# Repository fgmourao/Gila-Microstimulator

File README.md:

# 🦎 Gila Monster 
### Constant-Current Stimulator v1.0 

> **Under development**

An electrical microstimulator for constant-current biphasic (or monophasic) stimulation. Pulse timing is generated by the firmware running on an Arduino Uno (Pulse_generator_bifasic.ino).

The hardware is based on and adapted from the [Open-Stim](https://github.com/Open-Stim/openstim) project (UFSJ / LINNCE). In the original architecture, four Arduino outputs (Timer4) time the pulses with 10 µs resolution, and the analog circuit combines these signals into a controlled current. In the present design, only two outputs are used: the firmware directly generates the two stimulation phases, Phase A (D7) and Phase B (D8), with their edges positioned in software. Built on the [Gila-Pulse-Generator](https://github.com/fgmourao/Gila-Pulse-Generator), this version adds a second output port (D8). Every pulse of the selected engine becomes a pair: port A rises, Pulse, port A falls, Delay, port B rises, Pulse, port B falls. The two pulses never overlap, and the delay between them is programmable from 10 µs upwards. All three stimulation modes, Continuous, Burst and NPS, and both Manual and Trigger operation are preserved.<br/>

## Main Modifications

- **User interface:** The Nextion touchscreen interface (Arduino Leonardo) was replaced with a 16×2 I2C LCD and rotary encoder (Arduino Uno), reducing power consumption and simplifying assembly.

- **Battery monitor:** The LM741/zener/LED battery-monitoring circuit was removed to reduce battery consumption.

- **Amplifiers:** TL072 op-amps were replaced with OPA2197 devices, providing rail-to-rail operation, low offset, and operation up to 36 V. This makes better use of the available supply voltage and increases the output compliance range.

- **Simplified signal chain:** The two inverting summing amplifiers (four Timer4 signals) were replaced by a single differential amplifier (A − B) followed by a buffer.

- **Current adjustment:** The resistor board was replaced by a 10-turn potentiometer with a dial and range selector (1 mA, 100 µA, and 10 µA), allowing direct current adjustment and readout.

- **Power supply:** ±18 V from four 9 V batteries (one 1N4007 per rail). The voltage reference and the Arduino each have their own 9 V battery.

- **Isolation:** A digital isolator (ISO7720F) separates the Arduino from the stimulation circuit. Its output side is powered by a REF5050 reference, which fixes the pulse amplitude at 5V.

- **Output protection:** A DC-blocking capacitor (CBLK, 66 µF ceramic) and "bleeder" resistor (RBLEED, 10 MΩ) at the output, pull-down resistors on the inputs, and a passive current limiter (two 1N5304 current-regulating diodes, ~1.8 mA).

- **Output enable:** PhotoMOS relays controlled by D9 connect the electrodes only during stimulation and short them at rest.

- **Compliance alarm:** Two LEDs (one per phase) light when the load exceeds the compliance limit and the current falls below the setpoint.

## Specifications

Values below come from circuit simulation.

- **Output current:** Up to 1 mA, with selectable ranges of 1 mA, 100 µA, and 10 µA. Use the lowest range that covers the desired current (1 mA: 100 µA–1 mA; 100 µA: 10–100 µA; 10 µA: below 10 µA).

- **Maximum load at 1 mA:** Approximately 16 kΩ with a ±18 V battery supply. A working load of up to 12 kΩ is recommended.

- **Compliance voltage:** Approximately 16 V with a ±18 V battery supply, including the ~1 V drop of the current limiter.

- **Battery-dependent compliance:** Maximum load follows approximately Load_max = Compliance / Current. At 1 mA, every 1 V decrease in compliance reduces the maximum load by approximately 1 kΩ. With each rail decreasing from approximately 19 V to 14 V over battery life, the corresponding maximum load is approximately 17 kΩ to 12 kΩ.

- **Frequency:** 0.10–500 Hz (firmware-limited).

- **Minimum phase duration:** 100 µs in Continuous and Burst modes; 50 µs in NPS mode (firmware-limited).

- **Maximum phase duration:** Firmware-limited, capped at 999.99 ms in all modes.
    - Biphasic: (Period − 100 µs − Delay) / 2
    - Monophasic: Period − 100 µs
    - Hardware limit: CBLK charges as I × t / C during each phase. At 1 mA into 10 kΩ, the maximum phase is approximately 460 ms.

- **Hardware limitation, charge accumulation (monophasic only):** In monophasic mode, all charge flows in the same direction and accumulates over the pulse train; RBLEED keeps it bounded. The steady-state voltage across CBLK is approximately I × duty cycle × RBLEED, reached with a time constant of RBLEED × CBLK (~11 min). At 1 mA, 100 µs phases and 4 Hz, this settles around 4 V, which must be subtracted from the available compliance. If I × duty cycle × RBLEED exceeds the compliance margin, the output saturates before steady state is reached. In balanced biphasic mode this does not occur. For a 4 µs mismatch at 1 mA and 4 Hz, the residual is about 0.16 V.

- **Long monophasic protocols:** If the protocol requires net charge, an optional jumper can short CBLK, making the output DC-coupled. This removes the DC protection, and the current limiter and output-enable stage remain the only safeguards.

## Author

Flavio Mourao (mourao.fg@gmail.com)  
CNPq/MCTI/FNDCT Call No. 21/2024 — Grant No. 446467/2024-3  
Federal University of Minas Gerais, Brazil

Development started: November 2025  
Last update: October 2026

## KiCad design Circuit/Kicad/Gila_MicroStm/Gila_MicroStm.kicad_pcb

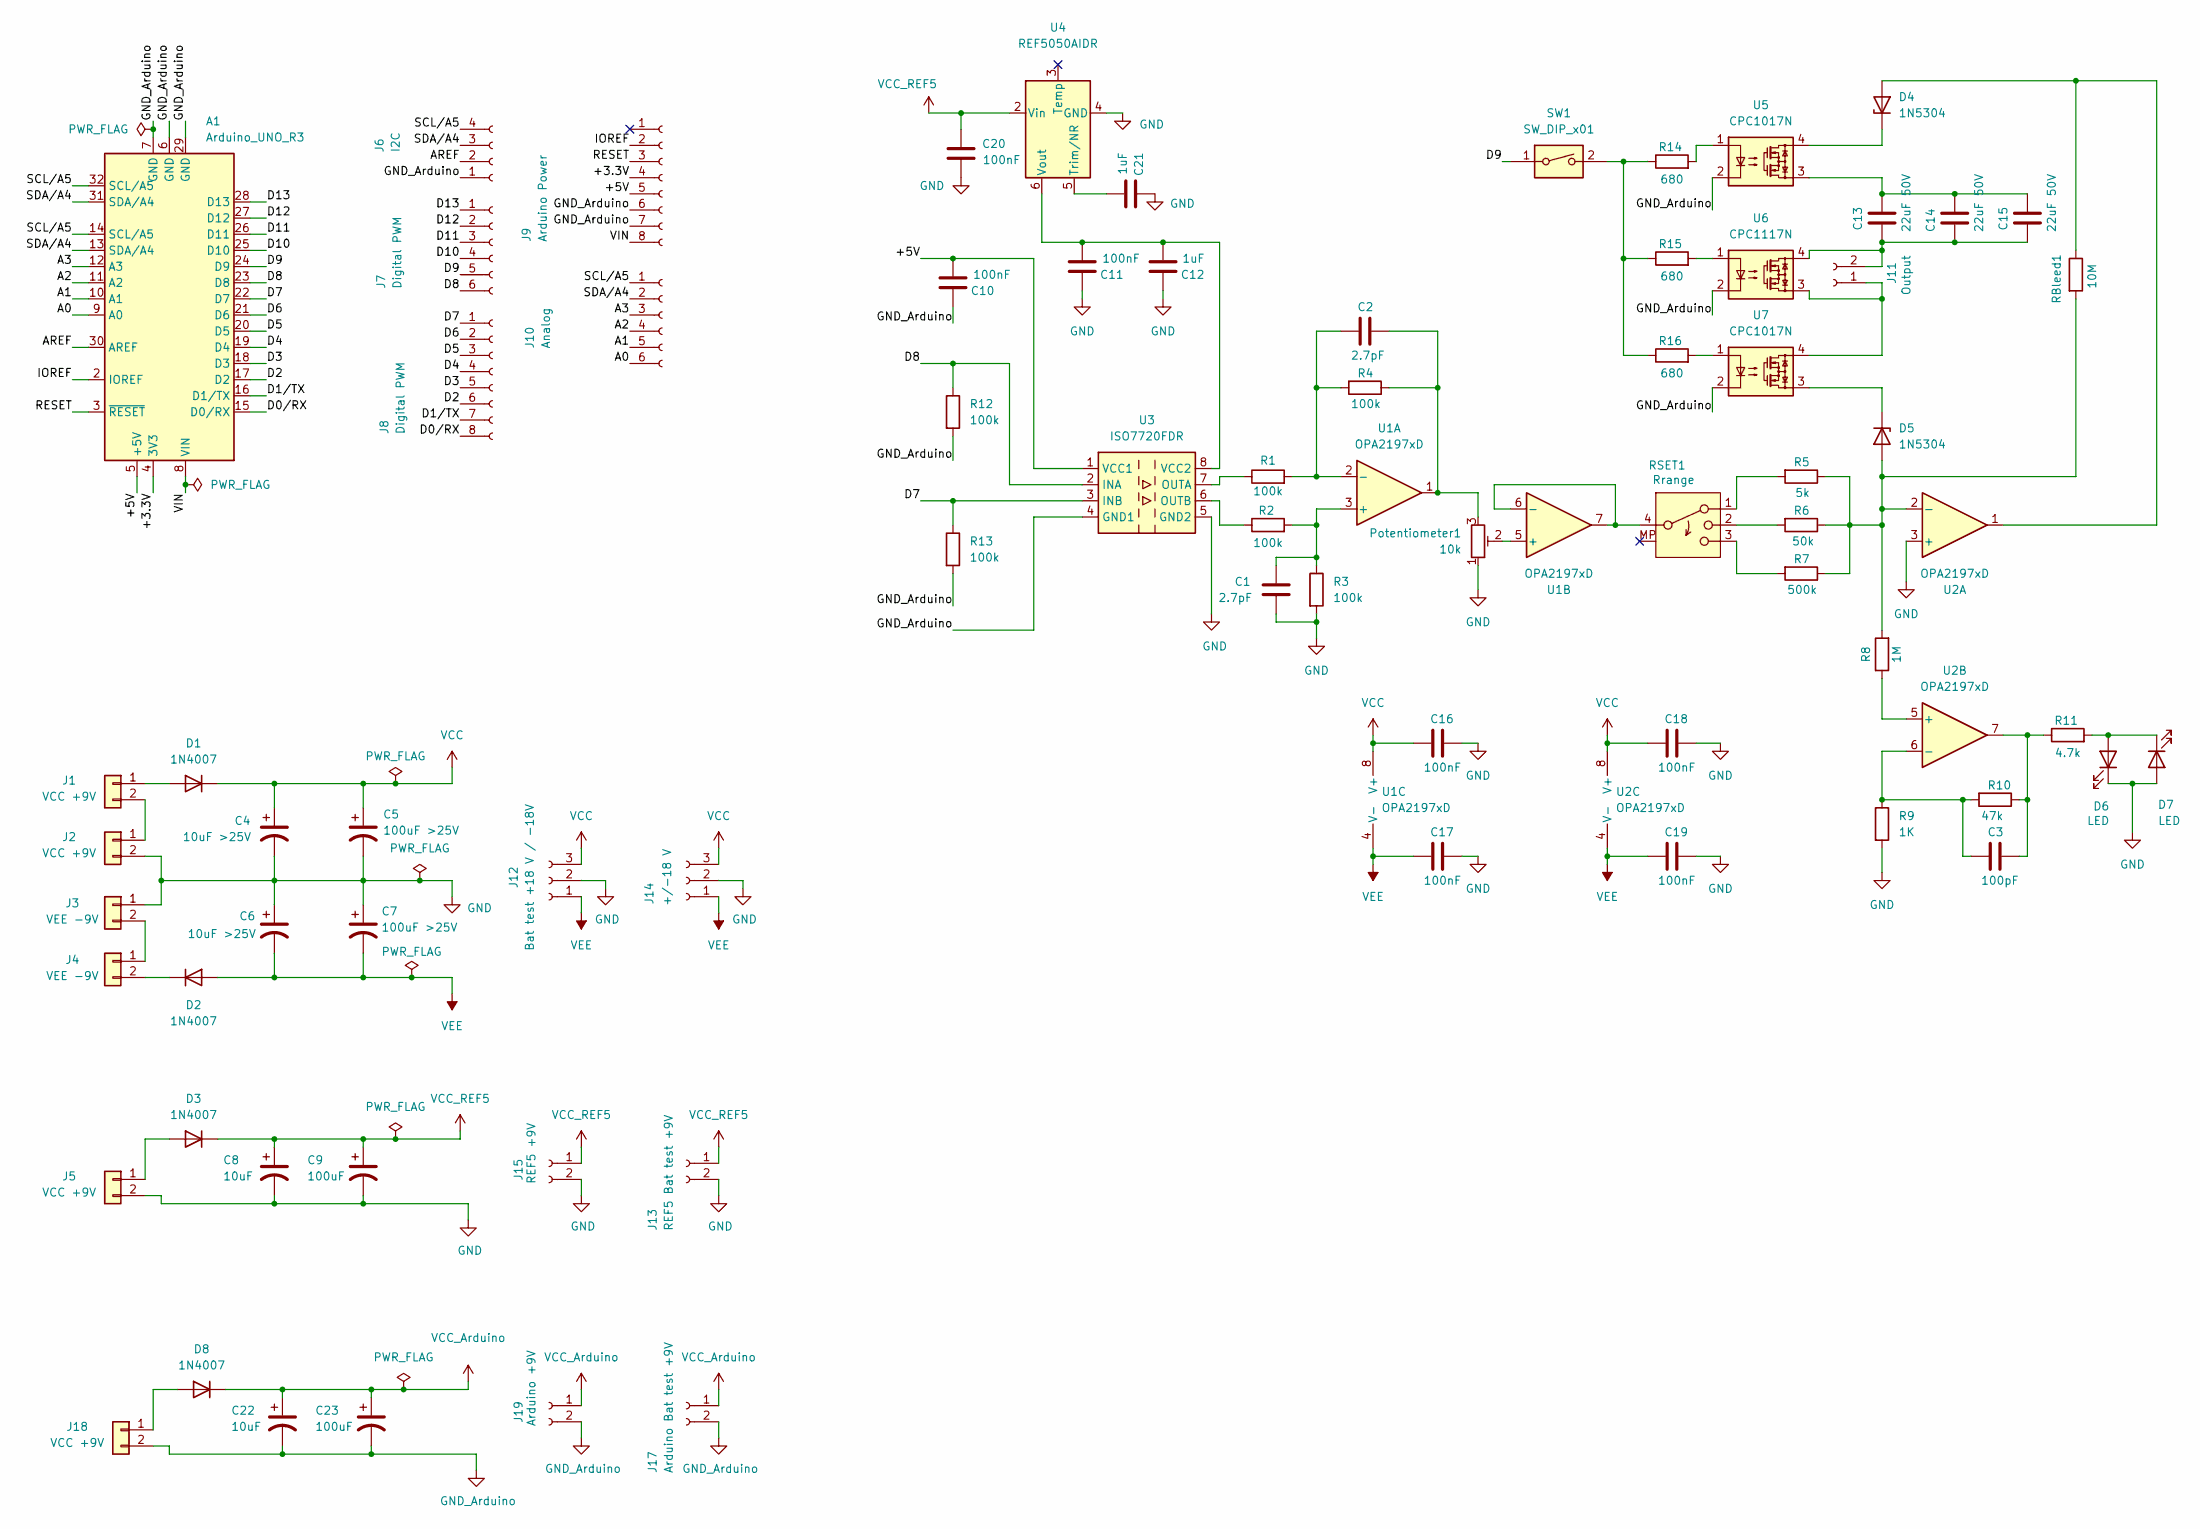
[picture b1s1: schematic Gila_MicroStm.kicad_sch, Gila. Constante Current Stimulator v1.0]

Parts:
A1: Arduino_UNO_R3
C1, C2: 2.7pF; C_0805_2012Metric
C3: 100pF; C_0805_2012Metric
C4, C6: 10uF >25V; CP_Elec_5x5.4
C5, C7: 100uF >25V; CP_Elec_8x10.5
C8, C22: 10uF; CP_Elec_5x5.4
C9, C23: 100uF; CP_Elec_8x10.5
C10, C11, C16, C17, C18, C19, C20: 100nF; C_0805_2012Metric
C12, C21: 1uF; C_0805_2012Metric
C13, C14, C15: 22uF 50V; C_0805_2012Metric
D1, D2, D3, D8: 1N4007; D_DO-41_SOD81_P10.16mm_Horizontal
D4, D5: 1N5304; D_DO-201AD_P3.81mm_Vertical_AnodeUp
D6, D7: LED; LED_D3.0mm_IRBlack
J1, J2, J5, J18: VCC +9V; PinHeader_1x02_P2.54mm_Horizontal
J3, J4: VEE -9V; PinHeader_1x02_P2.54mm_Horizontal
J6: I2C; PinSocket_1x04_P2.54mm_Vertical
J7: Digital PWM; PinHeader_1x06_P2.54mm_Vertical
J8: Digital PWM; PinHeader_1x08_P2.54mm_Vertical
J9: Arduino Power; PinSocket_1x08_P2.54mm_Vertical
J10: Analog; PinHeader_1x06_P2.54mm_Vertical
J11: Output; PinHeader_1x02_P2.54mm_Vertical
J12: Bat test +18 V / -18V; PinSocket_1x03_P2.54mm_Vertical
J13: REF5 Bat test +9V; PinSocket_1x02_P2.54mm_Vertical
J14: +/-18 V; PinSocket_1x03_P2.54mm_Vertical
J15: REF5 +9V; PinSocket_1x02_P2.54mm_Vertical
J17: Arduino Bat test +9V; PinSocket_1x02_P2.54mm_Vertical
J19: Arduino +9V; PinSocket_1x02_P2.54mm_Vertical
Potentiometer1: 10k; Potentiometer_ACP_CA6-H2,5_Horizontal
R1, R2, R3, R4, R12, R13: 100k; R_0805_2012Metric
R5: 5k; R_0805_2012Metric
R6: 50k; R_0805_2012Metric
R7: 500k; R_0805_2012Metric
R8: 1M; R_0805_2012Metric
R9: 1K; R_0805_2012Metric
R10: 47k; R_0805_2012Metric
R11: 4.7k; R_0805_2012Metric
R14, R15, R16: 680; R_0805_2012Metric
RBleed1: 10M; R_0805_2012Metric
RSET1: Rrange; PinHeader_1x04_P2.54mm_Vertical
SW1: SW_DIP_x01; PinHeader_1x02_P2.54mm_Vertical
U1, U2: OPA2197xD; SOIC-8_3.9x4.9mm_P1.27mm
U3: ISO7720FDR; SOIC-8_3.9x4.9mm_P1.27mm
U4: REF5050AIDR; SOIC-8_3.9x4.9mm_P1.27mm
U5, U7: CPC1017N; SOP-4_3.8x4.1mm_P2.54mm
U6: CPC1117N; SOP-4_3.8x4.1mm_P2.54mm

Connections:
/+3.3V: A1.4 (3V3), J9.4
/+5V: A1.5 (+5V), C10.1, J9.5, U3.1 (VCC1)
/A0: A1.9 (A0), J10.6
/A1: A1.10 (A1), J10.5
/A2: A1.11 (A2), J10.4
/A3: A1.12 (A3), J10.3
/AREF: A1.30 (AREF), J6.2
/D0/RX: A1.15 (D0/RX), J8.8
/D1/TX: A1.16 (D1/TX), J8.7
/D2: A1.17 (D2), J8.6
/D3: A1.18 (D3), J8.5
/D4: A1.19 (D4), J8.4
/D5: A1.20 (D5), J8.3
/D6: A1.21 (D6), J8.2
/D7: A1.22 (D7), J8.1, R13.1, U3.3 (INB)
/D8: A1.23 (D8), J7.6, R12.1, U3.2 (INA)
/D9: A1.24 (D9), J7.5, SW1.1
/D10: A1.25 (D10), J7.4
/D11: A1.26 (D11), J7.3
/D12: A1.27 (D12), J7.2
/D13: A1.28 (D13), J7.1
/IOREF: A1.2 (IOREF), J9.2
/RESET: A1.3 (~RESET), J9.3
/SCL/A5: A1.14 (SCL/A5), A1.32 (SCL/A5), J6.4, J10.1
/SDA/A4: A1.13 (SDA/A4), A1.31 (SDA/A4), J6.3, J10.2
/VIN: A1.8 (VIN), J9.8
GND: C1.1, C4.2, C5.2, C6.1, C7.1, C8.2, C9.2, C11.2, C12.2, C16.2, C17.2, C18.2, C19.2, C20.2, C21.2, D6.1 (K), D7.2 (A), J2.2, J3.1, J5.2, J12.2, J13.2, J14.2, J15.2, Potentiometer1.1, R3.2, R9.2, U2.3 (+), U3.5 (GND2), U4.4 (GND); also elsewhere on the board
GND_Arduino: A1.6 (GND), A1.7 (GND), A1.29 (GND), C10.2, C22.2, C23.2, J6.1, J9.6, J9.7, J17.2, J18.2, J19.2, R12.2, R13.2, U3.4 (GND1), U5.2, U6.2, U7.2
unnamed: C2.2, Potentiometer1.3, R4.1, U1.1
unnamed: C3.2, R10.1, R11.1, U2.7
unnamed: C13.2, C14.2, C15.2, U5.3
unnamed: D1.2 (A), J1.1
unnamed: D2.1 (K), J4.2
unnamed: D3.2 (A), J5.1
unnamed: D4.2 (A), RBleed1.1, U2.1
unnamed: D4.1 (K), U5.4
unnamed: D5.2 (A), R5.1, R6.1, R7.1, R8.2, RBleed1.2, U2.2 (-)
unnamed: D5.1 (K), U7.3
unnamed: D6.2 (A), D7.1 (K), R11.2
unnamed: D8.2 (A), J18.1
unnamed: J1.2, J2.1
unnamed: J3.2, J4.1
unnamed: J11.1, U6.3, U7.4
unnamed: C13.1, C14.1, C15.1, J11.2, U6.4
unnamed: R5.2, RSET1.1
unnamed: R6.2, RSET1.2
unnamed: R7.2, RSET1.3
unnamed: R14.1, R15.1, R16.1, SW1.2
unnamed: R14.2, U5.1
unnamed: R15.2, U6.1
unnamed: R16.2, U7.1
unnamed: C1.2, R2.2, R3.1, U1.3 (+)
unnamed: C2.1, R1.2, R4.2, U1.2 (-)
unnamed: Potentiometer1.2, U1.5 (+)
unnamed: RSET1.4, U1.6 (-), U1.7
unnamed: R8.1, U2.5 (+)
unnamed: C3.1, R9.1, R10.2, U2.6 (-)
unnamed: R1.1, U3.7 (OUTA)
unnamed: R2.1, U3.6 (OUTB)
unnamed: C11.1, C12.1, U3.8 (VCC2), U4.6 (Vout)
unnamed: C21.1, U4.5 (Trim/NR)
VCC: C4.1, C5.1, C16.1, C18.1, D1.1 (K), J12.3, J14.3, U1.8 (V+), U2.8 (V+); also elsewhere on the board
VCC_Arduino: C22.1, C23.1, D8.1 (K), J17.1, J19.1
VCC_REF5: C8.1, C9.1, C20.1, D3.1 (K), J13.1, J15.1, U4.2 (Vin); also elsewhere on the board
VEE: C6.2, C7.2, C17.1, C19.1, D2.2 (A), J12.1, J14.1, U1.4 (V-), U2.4 (V-); also elsewhere on the board

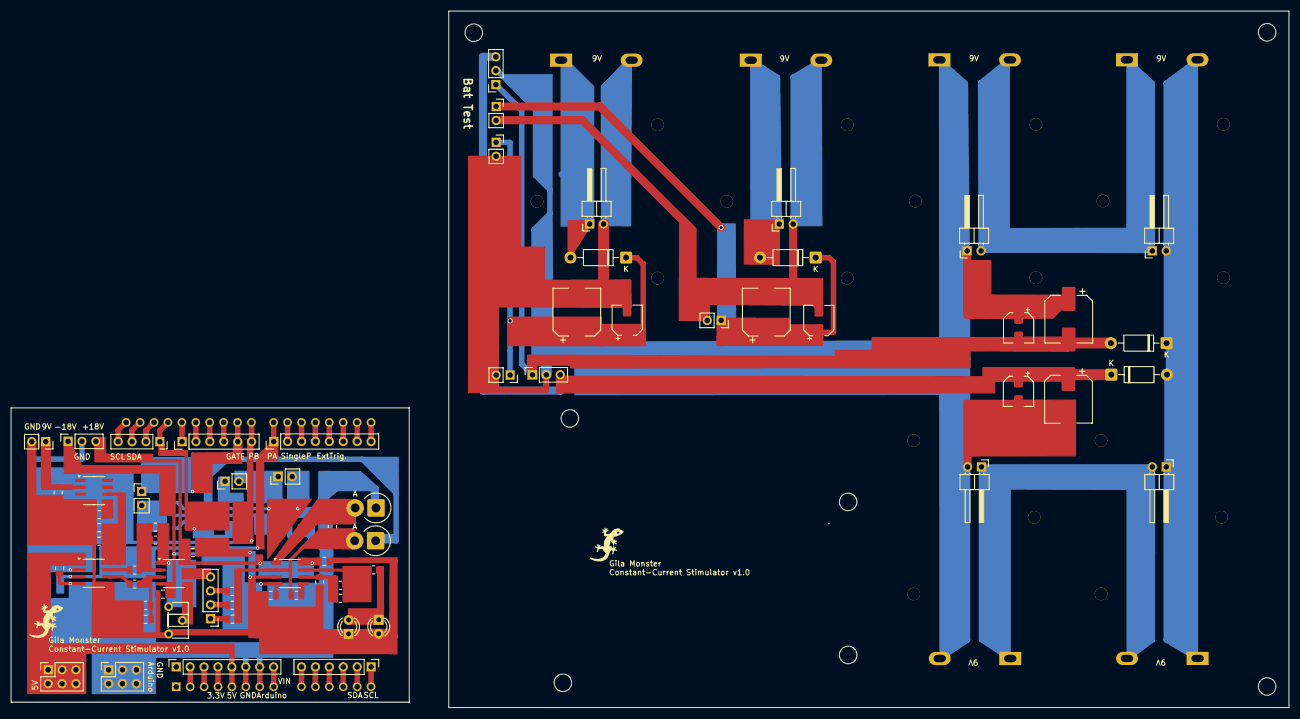
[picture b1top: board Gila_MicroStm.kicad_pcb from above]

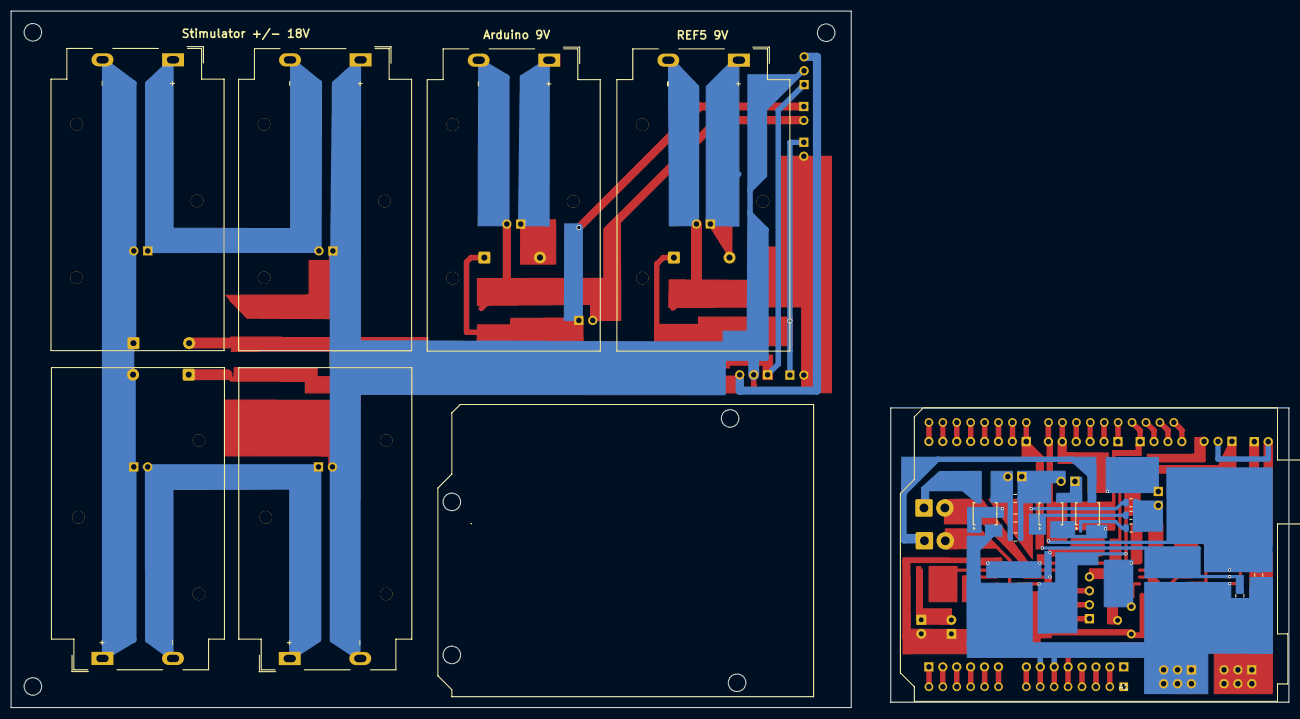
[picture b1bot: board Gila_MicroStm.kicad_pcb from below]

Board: 2 copper layers, 233.3 x 127.1 mm, 82 parts (12 on the bottom side), 65 nets.

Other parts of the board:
5V: 5V; PinSocket_2x03_P2.54mm_Vertical
A**: Arduino_Uno_R3_Shield_border
GNDArduino: GND Arduino; PinSocket_2x03_P2.54mm_Vertical
J14#2: +/-18 V; PinSocket_1x03_P2.54mm_Vertical
J15#2: REF5+9V; PinSocket_1x02_P2.54mm_Vertical

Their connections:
GND: J14#2.2, J15#2.2; also elsewhere on the board
VCC: J14#2.3; also elsewhere on the board
VCC_REF5: J15#2.1; also elsewhere on the board
VEE: J14#2.1; also elsewhere on the board
